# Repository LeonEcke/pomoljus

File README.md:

# Pomoljus Interval Timer

Pomoljus is a programmable sequential interval timer with a light based alert method. In other words, its a clock aimed to function in a way inspired by the Pomodoro technique using only RGB LEDs.

## Milestones

The development of the Pomoljus is slow and is lead by a single slow person. To keep the development pointing in the correct direction a series of more achievable milestones have are listed below. This can also give an idea of where the development of this project is.

[Insert PBI]

Here is a rough estimation of the three major areas of the Pomoljus development.

- Firmware
  - ▰▰▱▱▱▱▱▱▱▱▱▱▱▱▱▱▱▱▱▱ *[10%]*
- Electrical
  - ▰▰▰▰▰▱▱▱▱▱▱▱▱▱▱▱▱▱▱▱ *[25%]*
- Housing
  - ▱▱▱▱▱▱▱▱▱▱▱▱▱▱▱▱▱▱▱▱ *[00%]*

## Support

If you wish to shout encouraging words at me then you can find me at [@bpall@mstdn.social](https://mstdn.social/@bpall). You can also find my blog/project hub over at [bPall.se ](bPall.se).

## More

[My blog post about the initial concept generation.](https://bpall.se/blog/Pomljus%20Ch%200/)

---

## Getting it running

The Pomoljus is designed to run on an RP2040 using the [Raspberry Pi Pico C/C++ SDK](https://github.com/raspberrypi/pico-sdk). The LEDs are SK6812Minis. It's all mounted on custom designed PCBs created using KiCad. The housing is designed in [TBD].

Firmware files are found in `/firmware/`. Electrical diagrams and PCB design files are found in `/pcb/`. Housing and mechanical designs will live in `/cad/`.

### Building firmware from source

[Insert instructions on how to build...]

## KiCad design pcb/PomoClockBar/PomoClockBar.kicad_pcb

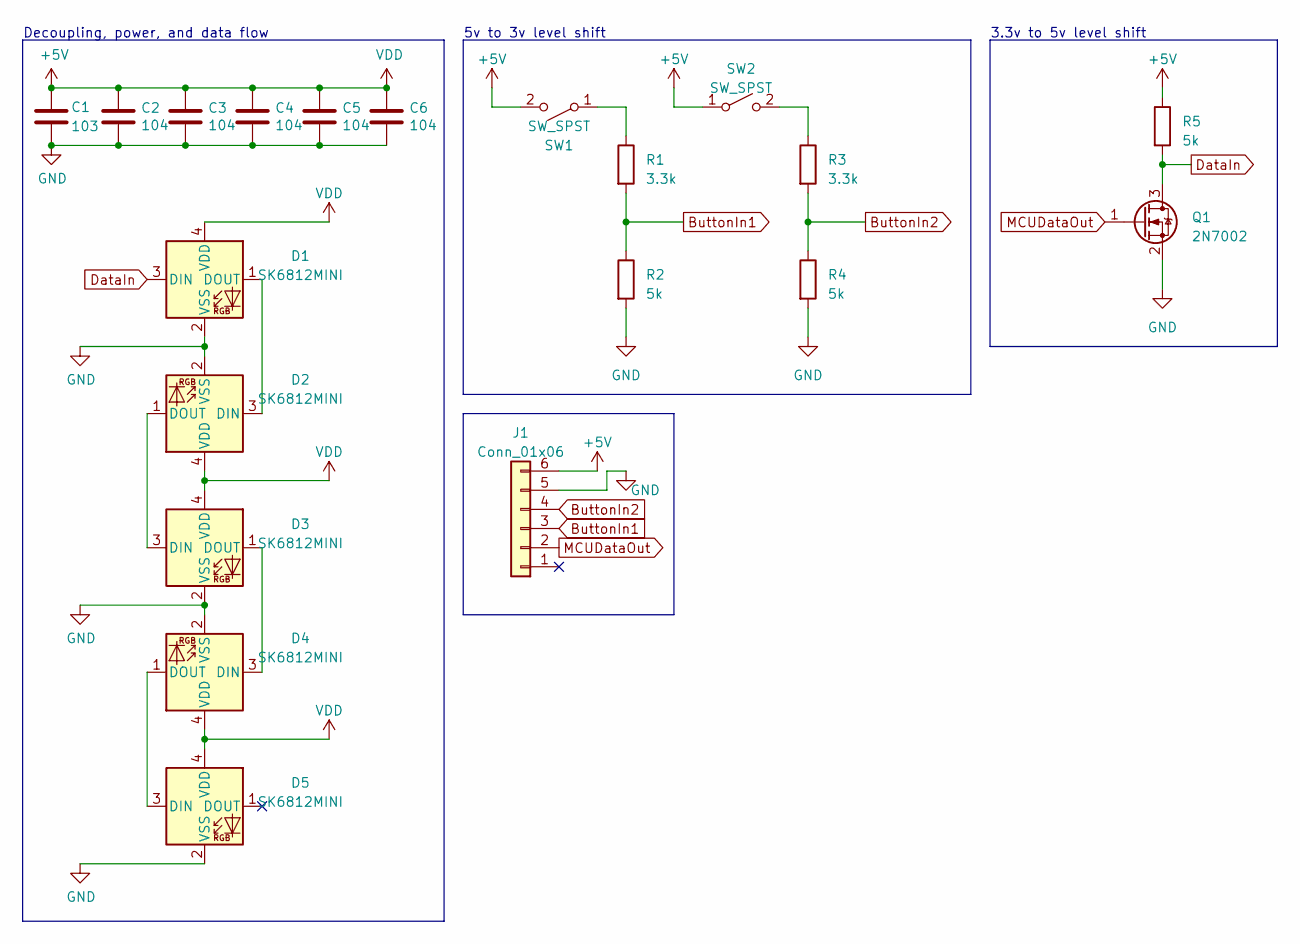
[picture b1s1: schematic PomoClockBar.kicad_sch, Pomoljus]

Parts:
C1: 103; C_0805_2012Metric_Pad1.18x1.45mm_HandSolder
C2, C3, C4, C5, C6: 104; C_0805_2012Metric_Pad1.18x1.45mm_HandSolder
D1, D2, D3, D4, D5: SK6812MINI; LED_SK6812MINI_PLCC4_3.5x3.5mm_P1.75mm
J1: Conn_01x06; JST_SH_SM06B-SRSS-TB_1x06-1MP_P1.00mm_Horizontal
Q1: 2N7002; SOT-23
R1, R3: 3.3k; R_0603_1608Metric_Pad0.98x0.95mm_HandSolder
R2, R4, R5: 5k; R_0603_1608Metric_Pad0.98x0.95mm_HandSolder
SW1, SW2: SW_SPST; MyButton

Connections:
+5V: C1.1, C2.1, C3.1, C4.1, C5.1, C6.1, D1.4 (VDD), D2.4 (VDD), D3.4 (VDD), D4.4 (VDD), D5.4 (VDD), J1.6, R5.1, SW1.2 (B), SW2.1 (A)
ButtonIn1: J1.3, R1.2, R2.1
ButtonIn2: J1.4, R3.2, R4.1
DataIn: D1.3 (DIN), Q1.3 (D), R5.2
GND: C1.2, C2.2, C3.2, C4.2, C5.2, C6.2, D1.2 (VSS), D2.2 (VSS), D3.2 (VSS), D4.2 (VSS), D5.2 (VSS), J1.5, Q1.2 (S), R2.2, R4.2
MCUDataOut: J1.2, Q1.1 (G)
unnamed: D1.1 (DOUT), D2.3 (DIN)
unnamed: D2.1 (DOUT), D3.3 (DIN)
unnamed: D3.1 (DOUT), D4.3 (DIN)
unnamed: D4.1 (DOUT), D5.3 (DIN)
unnamed: R1.1, SW1.1 (A)
unnamed: R3.1, SW2.2 (B)

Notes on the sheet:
3.3v to 5v level shift
Decoupling, power, and data flow
5v to 3v level shift

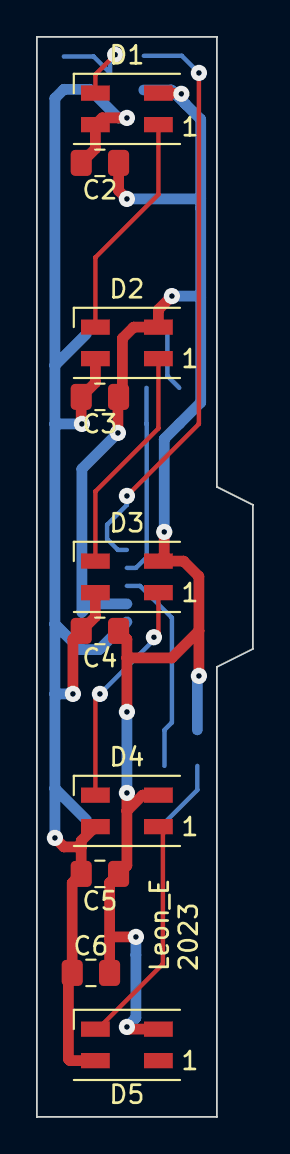
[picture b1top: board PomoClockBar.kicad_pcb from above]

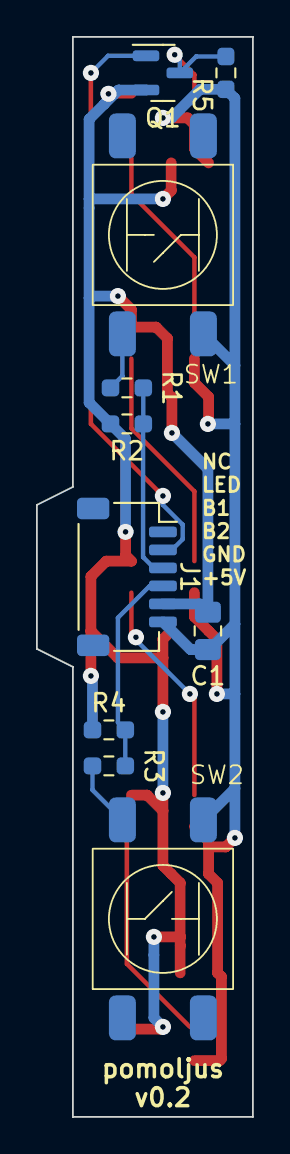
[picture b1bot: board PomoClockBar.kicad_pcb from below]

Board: 2 copper layers, 12.0 x 60.0 mm, 20 parts (10 on the bottom side), 12 nets.

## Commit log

2023-08-12 Initial Commit
    Add Readme file and the electrical design files that have been made
    up to this point.
2023-08-19 add firmware ignores
2023-08-19 add pico-sdk submodule
2023-08-19 add placeholder firmawre
    This is mainly to setup a CMake and submodule structure.
    Plug LED pin of board into pico pin 2.
2023-08-21 Refactor to use c++
2023-08-21 set c and c++ std to 17
2023-08-21 add local pi const
2023-08-23 implement HSV based colour interface & refactor
    refactored sk6812Driver to use hsv until last step.
    refactored src/CMakeLists to be more clear with two libraries.
    OBS, untested features: mix, to_hsv.
2023-08-24 add files for ledModifier
2023-08-24 Add interface function declarations
2023-08-25 Implement declarations for some modifier functions
    setPointers, setColour, changeHue, changeSaturation, changeValue
2023-08-26 add linebreak and offset parameter.
    Linebreak to respect 80char line limit
2023-08-27 add include to define uint8_t
2023-08-27 implement progress bar, fix minor errors
2023-08-30 Clean sk6812Driver.cpp of old implementation
2023-08-30 correct function pointer syntax
2023-08-30 Change tick related arguments to be ms.
    uint8_t -> uint16_t (should allow over a minute period time)
    period_time_sec -> ..._ms
2023-08-30 implement breathAnimation
2023-08-30 Add demo code for breathAnimation
2023-08-30 rename function
2023-08-30 change offset_ms to 16 bit
2023-08-30 implement waveAnimation
2023-08-30 add demo code for waveAnim.
2023-08-30 refactor for comments and row width
2023-08-30 correct inline documentation
2023-08-30 reformat code according to feedback
2023-08-30 add const for 255. Minor formatting
2023-08-30 add files
2023-08-30 Implement work mode, declare more modes.
2023-08-30 Refactor work mode and implement other progresses
    Internal generic is now used for all main progresser modes.
2023-08-30 add alarm and overtime
2023-08-30 reformat code
2023-08-30 change sk6812driver to demo ledModes
2023-08-30 tweak progress animation
2023-08-30 correct comments
2023-08-30 Add comments and remove magic numbers
2024-06-03 old. Implement ledController
